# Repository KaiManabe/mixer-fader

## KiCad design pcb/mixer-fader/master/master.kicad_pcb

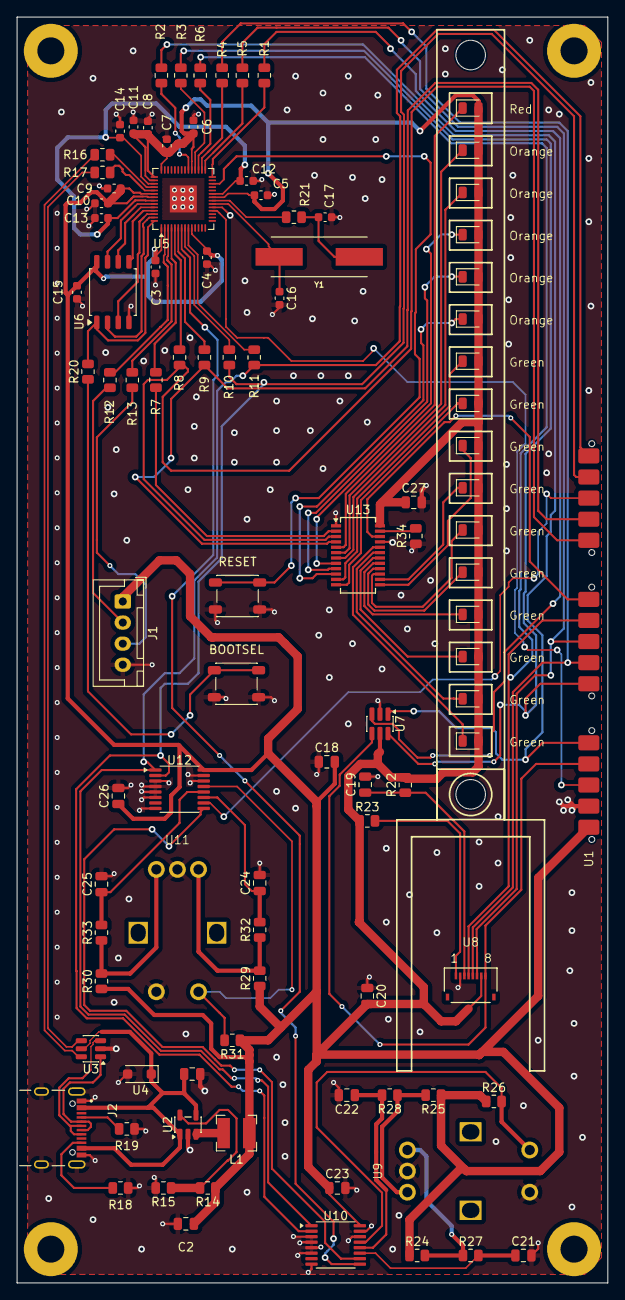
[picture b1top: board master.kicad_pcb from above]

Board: 2 copper layers, 70.0 x 150.0 mm, 81 parts (0 on the bottom side), 86 nets.

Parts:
BOOTSEL: BOOTSEL; SW_SPST_PTS647_Sx50
C1, C2: 10u; C_0805_2012Metric
C3, C4, C5, C6, C7, C8, C9, C10, C12, C13, C15: 0.1u; C_0603_1608Metric
C11, C14: 1u; C_0603_1608Metric
C16, C17: 27p; C_0603_1608Metric
C18, C19, C20, C23, C26, C27: 0.1u; C_0805_2012Metric
C21, C22, C24, C25: 0.01u; C_0805_2012Metric
J1: UART_SOCKET; JST_XH_B4B-XH-A_1x04_P2.50mm_Vertical
J2: UJ20-C-H-G-SMT-1-P16-TR
L1: 2.2u; L_Bourns-SRN4018
R1, R2, R3, R4, R5, R6, R7, R8, R9, R10, R11, R16, R17: 27; R_0805_2012Metric
R12, R13: 100; R_0805_2012Metric
R14: 453k; R_0805_2012Metric
R15: 100k; R_0805_2012Metric
R18, R19: 5.1k; R_0805_2012Metric
R20, R21: 1k; R_0805_2012Metric
R22, R24, R25, R26, R27, R28, R29, R30, R31, R32, R33: 10k; R_0805_2012Metric
R23: 18; R_0805_2012Metric
R34: 2.7k; R_0805_2012Metric
RESET: RESET; SW_SPST_PTS647_Sx50
U1: MixerFader_PogoPin_Male; 3x_PogoPinConnector_SMD_Male_01x05
U2: TLV62568DBV; SOT-23-5
U3: USBLC6-2SC6; SOT-23-6
U4: SMF5.0CA; D_SOD-123F
U5: RP2040; QFN-56-1EP_7x7mm_P0.4mm_EP3.2x3.2mm
U6: W25Q128JVS; SOIC-8_5.3x5.3mm_P1.27mm
U7: 74LVC1G175; SC-74-6_1.55x2.9mm_P0.95mm
U8: ST7735_FPC; ST7735_PFC_Inverted
U9, U11: EC11
U10, U12: 74LV165PW-Q100J; TSSOP-16_4.4x5mm_P0.65mm
U13: TLC59283DBQR; SSOP-24_3.9x8.7mm_P0.635mm
U14: LevelMeter_16
Y1: ABLS-12.000MHZ-B4-T

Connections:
+3V3: C2.1, C3.1, C4.1, C5.1, C6.1, C7.1, C8.1, C9.1, C10.1, C11.1, C15.1, C18.2, C20.2, C23.1, C26.1, C27.1, J1.1, L1.2, R14.1, R22.2, R23.1, R24.1, R25.1, R26.1, R29.1, R30.1, R31.1, U1.1 (3.3V), U5.1 (IOVDD), U5.10 (IOVDD), U5.22 (IOVDD), U5.33 (IOVDD), U5.42 (IOVDD), U5.43 (ADC_AVDD), U5.44 (VREG_VIN), U5.48 (USB_VDD), U5.49 (IOVDD), U6.8 (VCC), U7.5 (VCC), U8.7 (VCC), U10.16 (VCC), U12.16 (VCC), U13.24 (VCC), U14.2, U14.4, U14.6, U14.8, U14.10, U14.12, U14.14, U14.16, U14.18, U14.20, U14.22, U14.24, U14.26, U14.28, U14.30, U14.32
/Master_Display/DFF-CLK: R2.2, U1.5 (DISP_DFF_CLK), U7.1 (CLK)
/Master_Display/DFF-CLR: R3.2, U1.6 (DISP_DFF_CLR), U7.6 (~CLR)
/Master_Display/DFF-D: R1.2, U7.3 (D)
/Master_Display/DFF-Q: U1.4 (DISP_DFF_D), U7.4 (Q), U8.8 (CS)
/Master_Display/SPI-CLK: R5.2, U1.8 (DISP_SPI_CLK), U8.6 (SCL)
/Master_Display/SPI-DC: R6.2, U1.9 (DISP_DC), U8.4 (DC)
/Master_Display/SPI-MOSI: R4.2, U1.7 (DISP_SPI_MOSI), U8.5 (SDA)
/Master_LevelMeter/CLK: R8.2, U1.11 (LED_CLK), U13.3 (SCLK)
/Master_LevelMeter/DATA-IN: R7.2, U13.2 (SIN)
/Master_LevelMeter/DATA-OUT: U1.10 (LED_DATA), U13.22 (SOUT)
/Master_LevelMeter/LATCH: R9.2, U1.12 (LED_LATCH), U13.4 (LAT)
/Page_Encoder/CLK: R10.2, U1.14 (ENC_LATCH), U10.2 (CP), U12.2 (CP)
/Page_Encoder/DATA-IN: U1.13 (ENC_DATA), U12.10 (DS)
/Page_Encoder/DATA-OUT: U10.10 (DS), U12.9 (Q7)
/Page_Encoder/LATCH: R11.2, U1.15 (ENC_CLK), U10.1 (~PL), U12.1 (~PL)
/RP2040/1.1V: C12.1, C13.1, C14.1, U5.23 (DVDD), U5.45 (VREG_VOUT), U5.50 (DVDD)
/RP2040/GPIO0: R12.1, U5.2 (GPIO0)
/RP2040/GPIO1: R13.1, U5.3 (GPIO1)
/RP2040/GPIO2: R7.1, U5.4 (GPIO2)
/RP2040/GPIO3: R8.1, U5.5 (GPIO3)
/RP2040/GPIO4: R9.1, U5.6 (GPIO4)
/RP2040/GPIO5: U5.7 (GPIO5), U10.9 (Q7)
/RP2040/GPIO6: R10.1, U5.8 (GPIO6)
/RP2040/GPIO7: R11.1, U5.9 (GPIO7)
/RP2040/GPIO15: U1.3 (DISP_LOOPBACK), U5.18 (GPIO15)
/RP2040/GPIO17: R1.1, U5.28 (GPIO17)
/RP2040/GPIO18: R5.1, U5.29 (GPIO18)
/RP2040/GPIO19: R4.1, U5.30 (GPIO19)
/RP2040/GPIO20: R6.1, U5.31 (GPIO20)
/RP2040/GPIO21: R3.1, U5.32 (GPIO21)
/RP2040/GPIO22: R2.1, U5.34 (GPIO22)
/RP2040/QSPI_SCLK: U5.52 (QSPI_SCLK), U6.6 (CLK)
/RP2040/QSPI_SD0: U5.53 (QSPI_SD0), U6.5 (DI/IO_{0})
/RP2040/QSPI_SD1: U5.55 (QSPI_SD1), U6.2 (DO/IO_{1})
/RP2040/QSPI_SD2: U5.54 (QSPI_SD2), U6.3 (~WP/IO_{2})
/RP2040/QSPI_SD3: U5.51 (QSPI_SD3), U6.7 (~HOLD/~RESET/IO_{3})
/RP2040/RUN: RESET.1, U5.26 (RUN)
/RP2040/USB_DN: R16.1, U3.6 (I/O1)
/RP2040/USB_DP: R17.1, U3.4 (I/O2)
/RP2040/USB_VBUS: C1.1, J2.A4_B9 (VBUS), J2.B4_A9 (VBUS__1), U2.1 (EN), U2.4 (VIN), U3.5 (VBUS), U4.1
/RP2040/XIN: C16.1, U5.20 (XIN), Y1.1
/RP2040/XOUT: R21.2, U5.21 (XOUT)
/RP2040/~QSPI_SS: R20.2, U5.56 (~QSPI_SS), U6.1 (~CS)
/RP2040/~USB_BOOT: BOOTSEL.1, R20.1
GND: BOOTSEL.2, C1.2, C2.2, C3.2, C4.2, C5.2, C6.2, C7.2, C8.2, C9.2, C10.2, C11.2, C12.2, C13.2, C14.2, C15.2, C16.2, C17.2, C18.1, C19.2, C20.1, C21.2, C22.2, C23.2, C24.2, C25.2, C26.2, C27.2, J1.4, J2.A1_B12 (GND), J2.B1_A12 (GND__1), J2.SH1 (SHIELD), J2.SH2 (SHIELD__1), J2.SH3 (SHIELD__2), J2.SH4 (SHIELD__3), R15.2, R18.2, R19.2, R34.1, RESET.2, U1.2 (GND), U2.2 (GND), U3.2 (GND), U4.2, U5.19 (TESTEN), U5.57 (GND), U6.4 (GND), U7.2 (GND), U8.2 (GND), U9.C, U9.S1, U10.3 (D4), U10.4 (D5), U10.5 (D6), U10.6 (D7), U10.8 (GND), U10.14 (D3), U10.15 (~CE), U11.C, U11.S1, U12.3 (D4), U12.4 (D5), U12.5 (D6), U12.6 (D7), U12.8 (GND), U12.14 (D3), U12.15 (~CE), U13.1 (GND), U13.21 (BLANK)
unnamed: C17.1, R21.1, Y1.2
unnamed: J1.2, R12.2
unnamed: J1.3, R13.2
unnamed: J2.A5 (CC1), R19.1
unnamed: J2.B5 (CC2), R18.1
unnamed: J2.A7 (DN1), J2.B7 (DN2), U3.1 (I/O1)
unnamed: J2.A6 (DP1), J2.B6 (DP2), U3.3 (I/O2)
unnamed: R24.2, R27.1, U9.A
unnamed: R25.2, R28.1, U9.B
unnamed: R29.2, R32.1, U11.A
unnamed: R30.2, R33.1, U11.B
unnamed: R14.2, R15.1, U2.5 (FB)
unnamed: L1.1, U2.3 (SW)
unnamed: R16.2, U5.46 (USB_DM)
unnamed: R17.2, U5.47 (USB_DP)
unnamed: R23.2, U8.1 (LEDA)
unnamed: C19.1, R22.1, U8.3 (RESET)
unnamed: C21.1, R27.2, U10.11 (D0)
unnamed: C22.1, R28.2, U10.12 (D1)
unnamed: R26.2, U9.S2, U10.13 (D2)
unnamed: C24.1, R32.2, U12.11 (D0)
unnamed: C25.1, R33.2, U12.12 (D1)
unnamed: R31.2, U11.S2, U12.13 (D2)
unnamed: R34.2, U13.23 (IREF)
unnamed: U13.5 (OUT0), U14.1
unnamed: U13.6 (OUT1), U14.3
unnamed: U13.7 (OUT2), U14.5
unnamed: U13.8 (OUT3), U14.7
unnamed: U13.9 (OUT4), U14.9
unnamed: U13.10 (OUT5), U14.11
unnamed: U13.11 (OUT6), U14.13
unnamed: U13.12 (OUT7), U14.15
unnamed: U13.13 (OUT8), U14.17
unnamed: U13.14 (OUT9), U14.19
unnamed: U13.15 (OUT10), U14.21
unnamed: U13.16 (OUT11), U14.23
unnamed: U13.17 (OUT12), U14.25
unnamed: U13.18 (OUT13), U14.27
unnamed: U13.19 (OUT14), U14.29
unnamed: U13.20 (OUT15), U14.31

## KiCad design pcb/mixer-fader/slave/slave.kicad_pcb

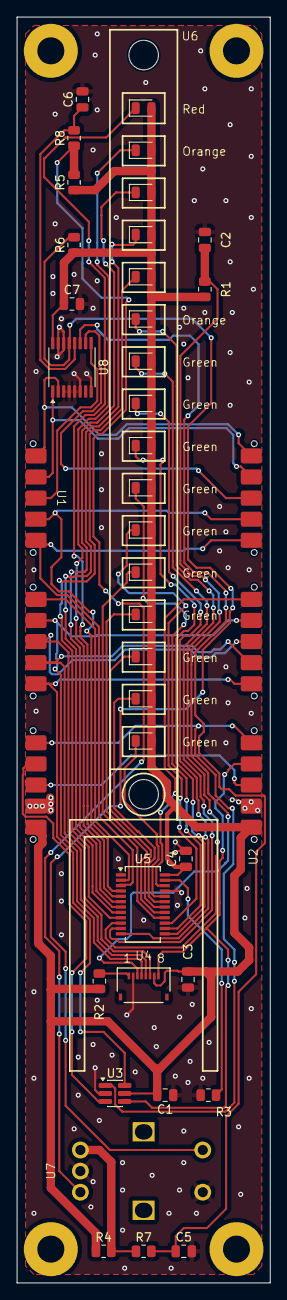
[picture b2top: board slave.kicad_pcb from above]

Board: 2 copper layers, 30.0 x 150.0 mm, 23 parts (0 on the bottom side), 42 nets.

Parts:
C1, C2, C3, C4, C7: 0.1u; C_0805_2012Metric
C5, C6: 0.01u; C_0805_2012Metric
R1, R4, R5, R6, R7, R8: 10k; R_0805_2012Metric
R2: 18; R_0805_2012Metric
R3: 2.7k; R_0805_2012Metric
U1: MixerFader_PogoPin_Female; 3x_PogoPinConnector_SMD_Female_01x05_1_1
U2: MixerFader_PogoPin_Male; 3x_PogoPinConnector_SMD_Male_01x05
U3: 74LVC1G175; SC-74-6_1.55x2.9mm_P0.95mm
U4: ST7735_FPC; ST7735_PFC_Inverted
U5: TLC59283DBQR; SSOP-24_3.9x8.7mm_P0.635mm
U6: LevelMeter_16
U7: EC11
U8: 74LV165PW-Q100J; TSSOP-16_4.4x5mm_P0.65mm

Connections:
+3V3: C1.2, C3.2, C4.1, C7.1, R1.2, R2.1, R4.1, R5.1, R6.1, U1.1 (3.3V), U2.1 (3.3V), U3.5 (VCC), U4.7 (VCC), U5.24 (VCC), U6.2, U6.4, U6.6, U6.8, U6.10, U6.12, U6.14, U6.16, U6.18, U6.20, U6.22, U6.24, U6.26, U6.28, U6.30, U6.32, U8.16 (VCC)
/Slave_Display/DFF-CLK: U1.5 (DISP_DFF_CLK), U2.5 (DISP_DFF_CLK), U3.1 (CLK)
/Slave_Display/DFF-CLR: U1.6 (DISP_DFF_CLR), U2.6 (DISP_DFF_CLR), U3.6 (~CLR)
/Slave_Display/DFF-D: U1.4 (DISP_DFF_D), U3.3 (D)
/Slave_Display/DFF-Q: U2.4 (DISP_DFF_D), U3.4 (Q), U4.8 (CS)
/Slave_Display/SPI-CLK: U1.8 (DISP_SPI_CLK), U2.8 (DISP_SPI_CLK), U4.6 (SCL)
/Slave_Display/SPI-DC: U1.9 (DISP_DC), U2.9 (DISP_DC), U4.4 (DC)
/Slave_Display/SPI-MOSI: U1.7 (DISP_SPI_MOSI), U2.7 (DISP_SPI_MOSI), U4.5 (SDA)
/Slave_Encoder/CLK: U1.15 (ENC_CLK), U2.15 (ENC_CLK), U8.2 (CP)
/Slave_Encoder/DATA-IN: U2.13 (ENC_DATA), U8.10 (DS)
/Slave_Encoder/DATA-OUT: U1.13 (ENC_DATA), U8.9 (Q7)
/Slave_Encoder/LATCH: U1.14 (ENC_LATCH), U2.14 (ENC_LATCH), U8.1 (~PL)
/Slave_LevelMeter/CLK: U1.11 (LED_CLK), U2.11 (LED_CLK), U5.3 (SCLK)
/Slave_LevelMeter/DATA-IN: U1.10 (LED_DATA), U5.2 (SIN)
/Slave_LevelMeter/DATA-OUT: U2.10 (LED_DATA), U5.22 (SOUT)
/Slave_LevelMeter/LATCH: U1.12 (LED_LATCH), U2.12 (LED_LATCH), U5.4 (LAT)
GND: C1.1, C2.2, C3.1, C4.2, C5.2, C6.2, C7.2, R3.1, U1.2 (GND), U2.2 (GND), U3.2 (GND), U4.2 (GND), U5.1 (GND), U5.21 (BLANK), U7.C, U7.S1, U8.3 (D4), U8.4 (D5), U8.5 (D6), U8.6 (D7), U8.8 (GND), U8.14 (D3), U8.15 (~CE)
unnamed: R4.2, R7.1, U7.A
unnamed: R5.2, R8.1, U7.B
unnamed: U1.3 (DISP_LOOPBACK), U2.3 (DISP_LOOPBACK)
unnamed: R2.2, U4.1 (LEDA)
unnamed: C2.1, R1.1, U4.3 (RESET)
unnamed: R3.2, U5.23 (IREF)
unnamed: U5.5 (OUT0), U6.1
unnamed: U5.6 (OUT1), U6.3
unnamed: U5.7 (OUT2), U6.5
unnamed: U5.8 (OUT3), U6.7
unnamed: U5.9 (OUT4), U6.9
unnamed: U5.10 (OUT5), U6.11
unnamed: U5.11 (OUT6), U6.13
unnamed: U5.12 (OUT7), U6.15
unnamed: U5.13 (OUT8), U6.17
unnamed: U5.14 (OUT9), U6.19
unnamed: U5.15 (OUT10), U6.21
unnamed: U5.16 (OUT11), U6.23
unnamed: U5.17 (OUT12), U6.25
unnamed: U5.18 (OUT13), U6.27
unnamed: U5.19 (OUT14), U6.29
unnamed: U5.20 (OUT15), U6.31
unnamed: C5.1, R7.2, U8.11 (D0)
unnamed: C6.1, R8.2, U8.12 (D1)
unnamed: R6.2, U7.S2, U8.13 (D2)

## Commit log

2026-01-04 Add all .gitignore
2026-01-04 Initialized KiCad project
2026-01-04 Add requirements-definition
2026-01-08 Add basic-design
2026-01-08 Add detailed-design of PCB
2026-01-08 Split KiCad project
2026-01-11 Add detailed-design of enclosure
2026-01-11 Add enclosure of level-meter
2026-01-11 Add enclosure of display
2026-01-11 Fix enclosure of display
2026-01-12 Add common symbols, footprints, sheets
2026-01-12 Add master pcb
2026-01-12 Add slave pcb
2026-01-12 Add endcap pcb
2026-01-12 Orderd PCB and Spacer, Window
2026-01-30 Add BOM
2026-01-30 Ordered Parts
2026-01-31 Initialized RP2040 Project
2026-03-09 Add Display/Encoder/LevelMeter Controllers
2026-03-10 Add USB communicators
2026-03-10 tmptmp
2026-04-04 tmptmptmp
2026-04-04 tmptmptmptmp
2026-04-04 awww
2026-04-05 最適化前
2026-04-12 codex最適化
